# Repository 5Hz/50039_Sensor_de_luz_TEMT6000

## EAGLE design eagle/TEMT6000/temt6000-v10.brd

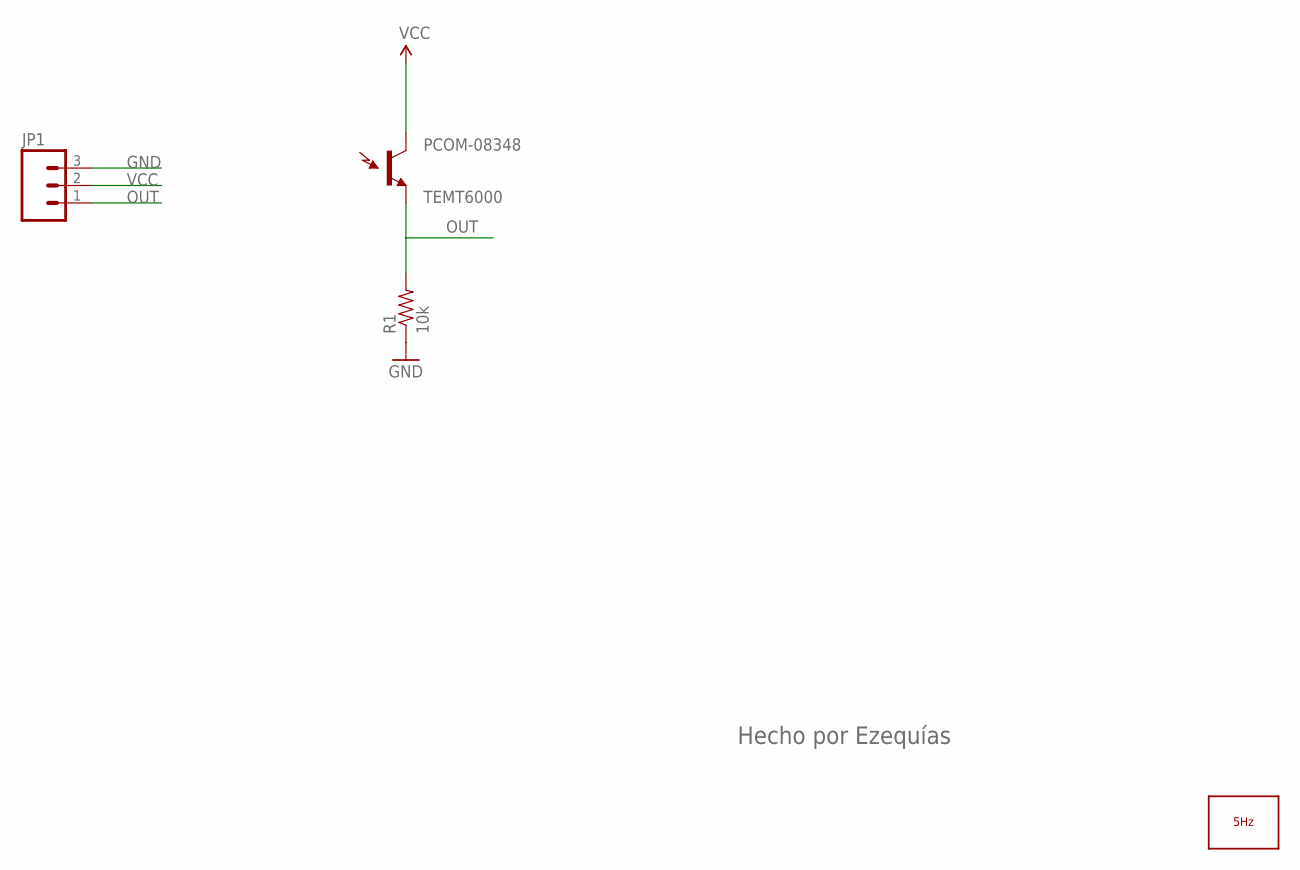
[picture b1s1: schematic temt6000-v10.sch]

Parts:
JP1: M03PTH; 1X03
LOGO1: LOGO_5HZ_H_5MM; 5HZ_LOGO_H_5MM
PCOM-08348: TEMT6000; TEMT6000-SEN
R1: 10k; 0603-RES

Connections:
GND: JP1.3, R1.1
OUT: JP1.1, PCOM-08348.EMITTER (E1), R1.2
VCC: JP1.2, PCOM-08348.COLLECTOR (C1)

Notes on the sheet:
Hecho por Ezequías

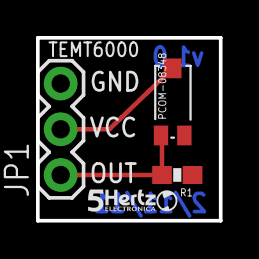
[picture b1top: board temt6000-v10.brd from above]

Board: 2 copper layers, 10.2 x 10.2 mm, 4 parts (0 on the bottom side), 3 nets.

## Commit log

2014-01-10 creación
